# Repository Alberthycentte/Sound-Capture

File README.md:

# Sound Capture Device - User Manual By Albert Hycentte

## 📖 Table of Contents
1. [Introduction](#introduction)
2. [Hardware Overview](#hardware-overview)
3. [Getting Started](#getting-started)
4. [Operating Instructions](#operating-instructions)
5. [LED Status Indicators](#led-status-indicators)
6. [Technical Specifications](#technical-specifications)
7. [Firmware Upload Guide](#firmware-upload-guide)
8. [Troubleshooting](#troubleshooting)
9. [File Management](#file-management)
10. [Maintenance & Care](#maintenance--care)
11. [Advanced Configuration](#advanced-configuration)
12. [Safety Information](#safety-information)

---

## 🎤 Introduction

Welcome to the **Sound Capture Device**! This portable audio recorder allows you to:
- Record high-quality audio with a professional MEMS microphone
- Store recordings as standard WAV files on an SD card
- Play back recordings through a built-in amplifier and speaker
- Operate on battery power or USB for extended recording sessions

This device is perfect for voice memos, field recordings, interviews, lectures, music practice, or any situation where you need reliable audio capture.

---

## 🔧 Hardware Overview

### Main Components

| Component | Description | Location |
|-----------|-------------|----------|
| **ESP32-S3** | Main processor | Center of PCB |
| **INMP441** | MEMS microphone | Bottom right of board |
| **MAX98357A** | Class D audio amplifier | Near speaker connector |
| **SD Card Slot** | Storage for recordings | Bottom left edge |
| **USB-C Port** | Power & programming | Top-left corner |
| **Battery Connector** | LiPo battery input | Left side |
| **Speaker Connector** | 4-8Ω speaker output | Left side |

### User Interface

#### Buttons (Bottom Edge)
```
[START]  [STOP]  [PLAY]  [BOOT]  [EN]
   │       │       │       │      │
   │       │       │       │      └─── Reset button
   │       │       │       └────────── Programming mode
   │       │       └────────────────── Play last recording
   │       └────────────────────────── Stop recording/playback
   └────────────────────────────────── Start recording
```

#### Status LED
- Located near buttons
- Provides visual feedback for all operations
- See [LED Status Indicators](#led-status-indicators) for details

---

## 🚀 Getting Started

### What You Need

**Essential:**
- ✅ Sound Capture Device
- ✅ MicroSD card (4GB - 32GB, FAT32 formatted)
- ✅ USB-C cable (for charging/programming)
- ✅ 4Ω or 8Ω speaker (2-3W rating)

**Optional:**
- 🔋 3.7V LiPo battery (1000-2000mAh recommended)
- 💻 Computer (for firmware updates)

### Initial Setup

#### Step 1: Insert SD Card
1. Power off the device
2. Insert microSD card into slot (gold contacts facing down)
3. Push until it clicks into place
4. **Important:** Card must be formatted as FAT32

#### Step 2: Connect Speaker
1. Locate the 2-pin speaker connector (SPK)
2. Connect speaker wires 
3. Use 4Ω or 8Ω speaker rated for 2-3W

#### Step 3: Power Connection

**Option A: USB Power**
- Connect USB-C cable to device
- Connect other end to USB power adapter or computer
- LED should blink twice on startup

**Option B: Battery Power**
- Connect 3.7V LiPo battery to J2 connector
- Observe polarity: RED (+), BLACK (-)
- Battery charges automatically when USB connected

#### Step 4: First Power-On
1. Connect power source
2. Wait for LED indicators:
   - 2 blinks = System starting
   - 3 blinks = Ready to use
3. Device is now ready for recording!

---

## 🎵 Operating Instructions

### Recording Audio

**Basic Recording:**
1. **Press START button** once
   - LED turns ON (solid)
   - Recording begins immediately
2. Speak or capture audio (max 60 seconds)
3. **Press STOP button** to finish
   - LED blinks 2 times
   - File saved to SD card

**Recording Tips:**
- Speak clearly at normal volume
- Avoid covering microphone hole
- Recording stops automatically after 60 seconds
- Each recording creates a new numbered file (`rec_1.wav`, `rec_2.wav`, etc.)

### Playing Back Audio

**Playing Last Recording:**
1. **Press PLAY button** once
   - LED blinks slowly (500ms intervals)
   - Last recorded file plays automatically
2. Audio plays through connected speaker
3. Playback stops automatically at end
   - Or press STOP button to interrupt

**Volume:**
- Volume is set by hardware (12dB gain)
- To adjust, modify GAIN_SLOT resistor (see Advanced Configuration)

### Stopping Operations

**Stop Recording or Playback:**
- **Press STOP button** at any time
- Current operation terminates immediately
- LED blinks to confirm stop
- File is saved (if recording) before stopping

---

## 💡 LED Status Indicators

Understanding the status LED helps you know what the device is doing:

| LED Pattern | Meaning | Action |
|-------------|---------|--------|
| **2 blinks on power-up** | System initializing | Wait 2-3 seconds |
| **3 quick blinks** | System ready | Device ready to use |
| **Solid ON** | Recording in progress | Recording audio |
| **Slow blink (500ms)** | Playing audio | Playback in progress |
| **2 blinks after stop** | File saved successfully | Recording complete |
| **3 blinks (play press)** | No recordings found | Record something first |
| **5 rapid blinks** | Error detected | Check SD card or connections |
| **Continuous rapid blinks** | Critical error | Check troubleshooting section |

---

## 📊 Technical Specifications

### Audio Performance
| Parameter | Specification |
|-----------|---------------|
| **Sample Rate** | 16 kHz (voice optimized) |
| **Bit Depth** | 16-bit |
| **Channels** | Mono |
| **Format** | WAV (PCM uncompressed) |
| **Frequency Response** | 50 Hz - 8 kHz |
| **Microphone SNR** | 61 dB |
| **Amplifier Output** | 3.2W @ 4Ω, 1.4W @ 8Ω |
| **THD+N** | < 1% @ 1kHz |

### Recording Capacity
| SD Card Size | Recording Time @ 16kHz |
|--------------|------------------------|
| 4 GB | ~74 hours |
| 8 GB | ~148 hours |
| 16 GB | ~296 hours |
| 32 GB | ~592 hours |

**File Size:** Approximately 1.8 MB per minute of recording

### Power Specifications
| Mode | Current Draw | Battery Life (1000mAh) |
|------|--------------|------------------------|
| **Idle** | 50 mA | ~20 hours |
| **Recording** | 150 mA | ~6.5 hours |
| **Playback (medium volume)** | 250 mA | ~4 hours |
| **Charging** | Up to 1000 mA | ~1.5 hours |

### Physical Specifications
- **Supply Voltage:** 5V USB or 3.7V LiPo battery
- **Operating Temperature:** 0°C to 50°C
- **Storage Temperature:** -20°C to 60°C
- **Humidity:** 10% to 85% non-condensing

---

## 💻 Firmware Upload Guide

### Prerequisites

**Software Requirements:**
- Visual Studio Code (recommended) or Arduino IDE
- PlatformIO extension (for VS Code)
- USB-C cable
- Computer (Windows/Mac/Linux)

### Installation Steps

#### 1. Install PlatformIO
```bash
# For VS Code users:
1. Open VS Code
2. Go to Extensions (Ctrl+Shift+X)
3. Search "PlatformIO IDE"
4. Click Install

# For command line:
pip install platformio
```

#### 2. Prepare Project
```
Create folder structure:
sound_capture/
├── platformio.ini
├── src/
│   └── main.cpp
└── include/
```

#### 3. Configure platformio.ini
```ini
[env:esp32-s3-devkitc-1]
platform = espressif32
board = esp32-s3-devkitc-1
framework = arduino
upload_speed = 921600
monitor_speed = 115200
```

#### 4. Upload Firmware

**Method A: Using VS Code**
1. Connect USB-C cable to device
2. Hold **BOOT button** (GPIO0)
3. Press and release **EN button**
4. Release **BOOT button**
5. Click "Upload" in PlatformIO toolbar
6. Wait for "SUCCESS" message

**Method B: Command Line**
```bash
cd sound_capture
pio run --target upload
```

#### 5. Verify Upload
```bash
# Open serial monitor
pio device monitor

# You should see:
=== Sound Capture Device ===
Initializing...
System ready!
```

### Firmware Updates
To update firmware in the future:
1. Download new firmware release
2. Follow upload steps above
3. Your recordings on SD card are preserved
4. Settings may need reconfiguration

---

## 🔧 Troubleshooting

### SD Card Issues

**Problem: "SD card mount failed"**
- ✅ Check card is fully inserted
- ✅ Format card as FAT32 (not exFAT or NTFS)
- ✅ Try a different SD card
- ✅ Clean SD card contacts
- ✅ Use card 32GB or smaller

**Problem: "Failed to create file"**
- ✅ Check SD card is not write-protected
- ✅ Ensure card has free space
- ✅ Verify card is formatted correctly
- ✅ Try creating `/recordings` folder manually

### Audio Issues

**Problem: No sound when recording**
- ✅ Check microphone is not blocked
- ✅ Speak louder or move closer (6-12 inches)
- ✅ Verify INMP441 power (3.3V)
- ✅ Check GPIO36, 37, 38 connections
- ✅ Test with different recording

**Problem: No sound during playback**
- ✅ Verify speaker is connected
- ✅ Check speaker impedance (4-8Ω)
- ✅ Ensure volume is adequate (hardware gain)
- ✅ Test speaker with another device
- ✅ Check GPIO3 is enabling amplifier

**Problem: Distorted or garbled audio**
- ✅ Reduce volume (change GAIN_SLOT)
- ✅ Don't speak too close to microphone
- ✅ Check for loose connections
- ✅ Verify sample rate (16kHz default)
- ✅ Try re-recording

### Power Issues

**Problem: Device won't turn on**
- ✅ Check USB cable is connected
- ✅ Verify battery is charged
- ✅ Try different USB power source
- ✅ Check battery polarity
- ✅ Press EN button to reset

**Problem: Battery not charging**
- ✅ Ensure USB is connected
- ✅ Check charge LED (D5) is ON
- ✅ Verify battery polarity
- ✅ Battery may be fully charged
- ✅ Wait 1-2 hours for full charge

### Button Issues

**Problem: Buttons not responding**
- ✅ Press firmly and release
- ✅ Wait 200ms between presses (debounce)
- ✅ Check device is in IDLE state
- ✅ Reset device (EN button)
- ✅ Verify GPIO connections

### Error LED Patterns

**5 rapid blinks:**
1. Check SD card is inserted
2. Verify card is formatted FAT32
3. Check all connections
4. Re-upload firmware
5. Check serial monitor for details

---

## 📁 File Management

### File Structure
```
SD Card Root/
└── recordings/
    ├── rec_1.wav
    ├── rec_2.wav
    ├── rec_3.wav
    └── ...
```

### Accessing Recordings

**On Computer:**
1. Remove SD card from device
2. Insert into computer SD card reader
3. Navigate to `recordings` folder
4. Copy WAV files to computer
5. Files can be played with any media player

**Supported Players:**
- Windows Media Player
- VLC Media Player
- QuickTime (Mac)
- Any WAV-compatible software

### File Naming
- Files automatically numbered: `rec_1.wav`, `rec_2.wav`, etc.
- Device remembers last number used
- Deleting files resets numbering to highest existing number + 1

### Storage Management

**Checking Free Space:**
- Serial monitor shows card size on startup
- Monitor: "SD Card Size: XXXXMB"

**Deleting Old Recordings:**
1. Remove SD card
2. Connect to computer
3. Delete unwanted files from `/recordings/` folder
4. Re-insert card into device
5. Next recording continues numbering

**Backup Recommendations:**
- Copy recordings to computer regularly
- Keep SD card backups
- Card can be reformatted if needed (loses all data)

---

## 🛠️ Maintenance & Care

### Daily Use
- Keep device clean and dry
- Avoid extreme temperatures
- Don't cover microphone hole
- Store in protective case when not in use

### SD Card Care
- Don't remove card while recording
- Keep contacts clean
- Avoid static discharge
- Replace every 2-3 years for reliability

### Battery Maintenance
- Charge fully before first use
- Don't fully discharge (keep above 20%)
- Charge at room temperature
- Replace if runtime significantly decreases
- Store at 40-60% charge if unused for months

### Speaker Care
- Don't exceed 3W rating
- Avoid water exposure
- Check connections periodically
- Replace if sound becomes distorted

### Cleaning
- Use dry, soft cloth for exterior
- Don't use liquids near electronics
- Compressed air can clean microphone hole
- Clean SD card slot with dry brush

### Firmware Updates
- Check for updates periodically
- Updates may add features or fix bugs
- Follow upload guide for updates
- Backup recordings before updating

---

## ⚙️ Advanced Configuration

### Changing Audio Quality

**Location:** Line 51-54 in `main.cpp`

```cpp
// Voice recording (default)
#define SAMPLE_RATE    16000
#define SAMPLE_BITS    16
#define I2S_CHANNELS   1

// Music quality
#define SAMPLE_RATE    44100  // CD quality
#define SAMPLE_BITS    16
#define I2S_CHANNELS   1      // or 2 for stereo

// Phone quality (smaller files)
#define SAMPLE_RATE    8000
```

**Effect on file size:**
- 8 kHz: ~0.9 MB/min
- 16 kHz: ~1.8 MB/min
- 44.1 kHz: ~5 MB/min

### Adjusting Recording Time

**Location:** Line 54 in `main.cpp`

```cpp
#define RECORD_TIME_MS  60000  // 60 seconds

// Change to:
#define RECORD_TIME_MS  120000  // 2 minutes
#define RECORD_TIME_MS  300000  // 5 minutes
```

### Volume Adjustment (Hardware)

**Current Configuration:**
- GAIN_SLOT connected to VSYST (5V) via 0Ω resistor (R23)
- This provides 12dB gain

**To Change Volume:**

| R23 Connection | Gain | Volume |
|----------------|------|--------|
| GND | 9dB | Quieter |
| +3.3V | 12dB | Normal (current) |
| 100K to GND | 15dB | Louder |
| Open (DNP) | 18dB | Maximum |

**To modify:** Remove R23 and connect to desired voltage

### Custom File Naming

**Location:** Line 382 in `main.cpp`

```cpp
// Default naming
currentFileName = "/recordings/rec_" + String(recordingNumber) + ".wav";

// Custom naming examples:
currentFileName = "/recordings/audio_" + String(recordingNumber) + ".wav";
currentFileName = "/recordings/memo_" + String(millis()) + ".wav";
```

### Buffer Size Optimization

**Location:** Line 57 in `main.cpp`

```cpp
#define DMA_BUF_LEN    512  // Default

// For better quality, increase:
#define DMA_BUF_LEN    1024

// For lower latency, decrease:
#define DMA_BUF_LEN    256
```

**Note:** Larger buffers = smoother recording but more memory usage

---

## ⚠️ Safety Information

### Electrical Safety
- ⚡ Use only 5V USB power supply
- ⚡ Battery: 3.7V LiPo only (1000-2000mAh)
- ⚡ Observe battery polarity
- ⚡ Don't short-circuit battery terminals
- ⚡ Disconnect power during repairs

### Battery Safety
- 🔋 Use quality LiPo batteries with protection circuit
- 🔋 Don't puncture, crush, or disassemble battery
- 🔋 Keep away from heat/fire
- 🔋 Don't charge unattended
- 🔋 Dispose properly at recycling center

### Operating Precautions
- 💧 Not waterproof - avoid moisture
- 🌡️ Don't use in extreme temperatures
- 👂 Avoid excessive speaker volume near ears
- 🎤 Microphone not for medical/safety-critical use
- 📱 May interfere with sensitive equipment

### Environmental
- ♻️ Dispose of electronics responsibly
- ♻️ Recycle batteries at designated facilities
- ♻️ Keep away from children and pets
- ♻️ Follow local e-waste regulations

---

## 📞 Support & Resources

### Getting Help
1. Check this manual first
2. Review troubleshooting section
3. Check serial monitor for error messages
4. Verify all connections
5. Try known-good components (SD card, battery, etc.)

### Technical Support
- **Serial Monitor:** Connect USB and run `pio device monitor`
- **Debug Output:** Detailed startup and operation info
- **Error Messages:** Specific problem indicators

### Additional Resources
- **ESP32-S3 Datasheet:** Technical specifications
- **INMP441 Datasheet:** Microphone specifications
- **MAX98357A Datasheet:** Amplifier details
- **PlatformIO Documentation:** Development environment

---

## 📄 Specifications Summary

| Category | Details |
|----------|---------|
| **Processor** | ESP32-S3 Dual-core @ 240MHz |
| **Memory** | 512KB RAM, 16MB Flash |
| **Microphone** | INMP441 MEMS I2S |
| **Amplifier** | MAX98357A Class D, 3.2W |
| **Storage** | MicroSD up to 32GB |
| **Power** | USB-C 5V or 3.7V LiPo |
| **Battery** | 1000-2000mAh (4-6 hours) |
| **Audio Format** | 16kHz, 16-bit, Mono WAV |
| **Dimensions** | 60mm × 90mm (approximate) |
| **Weight** | ~50g (without battery) |

---

## 🎓 Quick Start Guide

**First-Time Users:**
1. ✅ Insert FAT32-formatted SD card
2. ✅ Connect 4-8Ω speaker
3. ✅ Connect USB-C power or battery
4. ✅ Wait for 3 LED blinks (ready)
5. ✅ Press START to record
6. ✅ Press STOP when done
7. ✅ Press PLAY to listen
8. ✅ Enjoy your recordings!

---

## 📜 Version History

**v1.0.0** (Current)
- Initial release
- Basic record/play/stop functionality
- WAV file format support
- Auto-numbering system
- Power management
- Status LED indicators

---

## 📝 Notes

- Device designed for voice recording applications
- Not intended for professional music production
- Recordings are mono (single channel)
- Maximum 60 seconds per recording (configurable)
- SD card required for operation
- Speaker required for playback
- Battery optional (can run from USB)

---

**Thank you for choosing the Sound Capture Device!**

For firmware updates, bug reports, or feature requests, please refer to the project repository or contact technical support.

**Happy Recording! 🎤🎵**

---

*Manual Version: 1.0.0*  
*Last Updated: 2025*  
*Compatible with Firmware: v1.0.0*

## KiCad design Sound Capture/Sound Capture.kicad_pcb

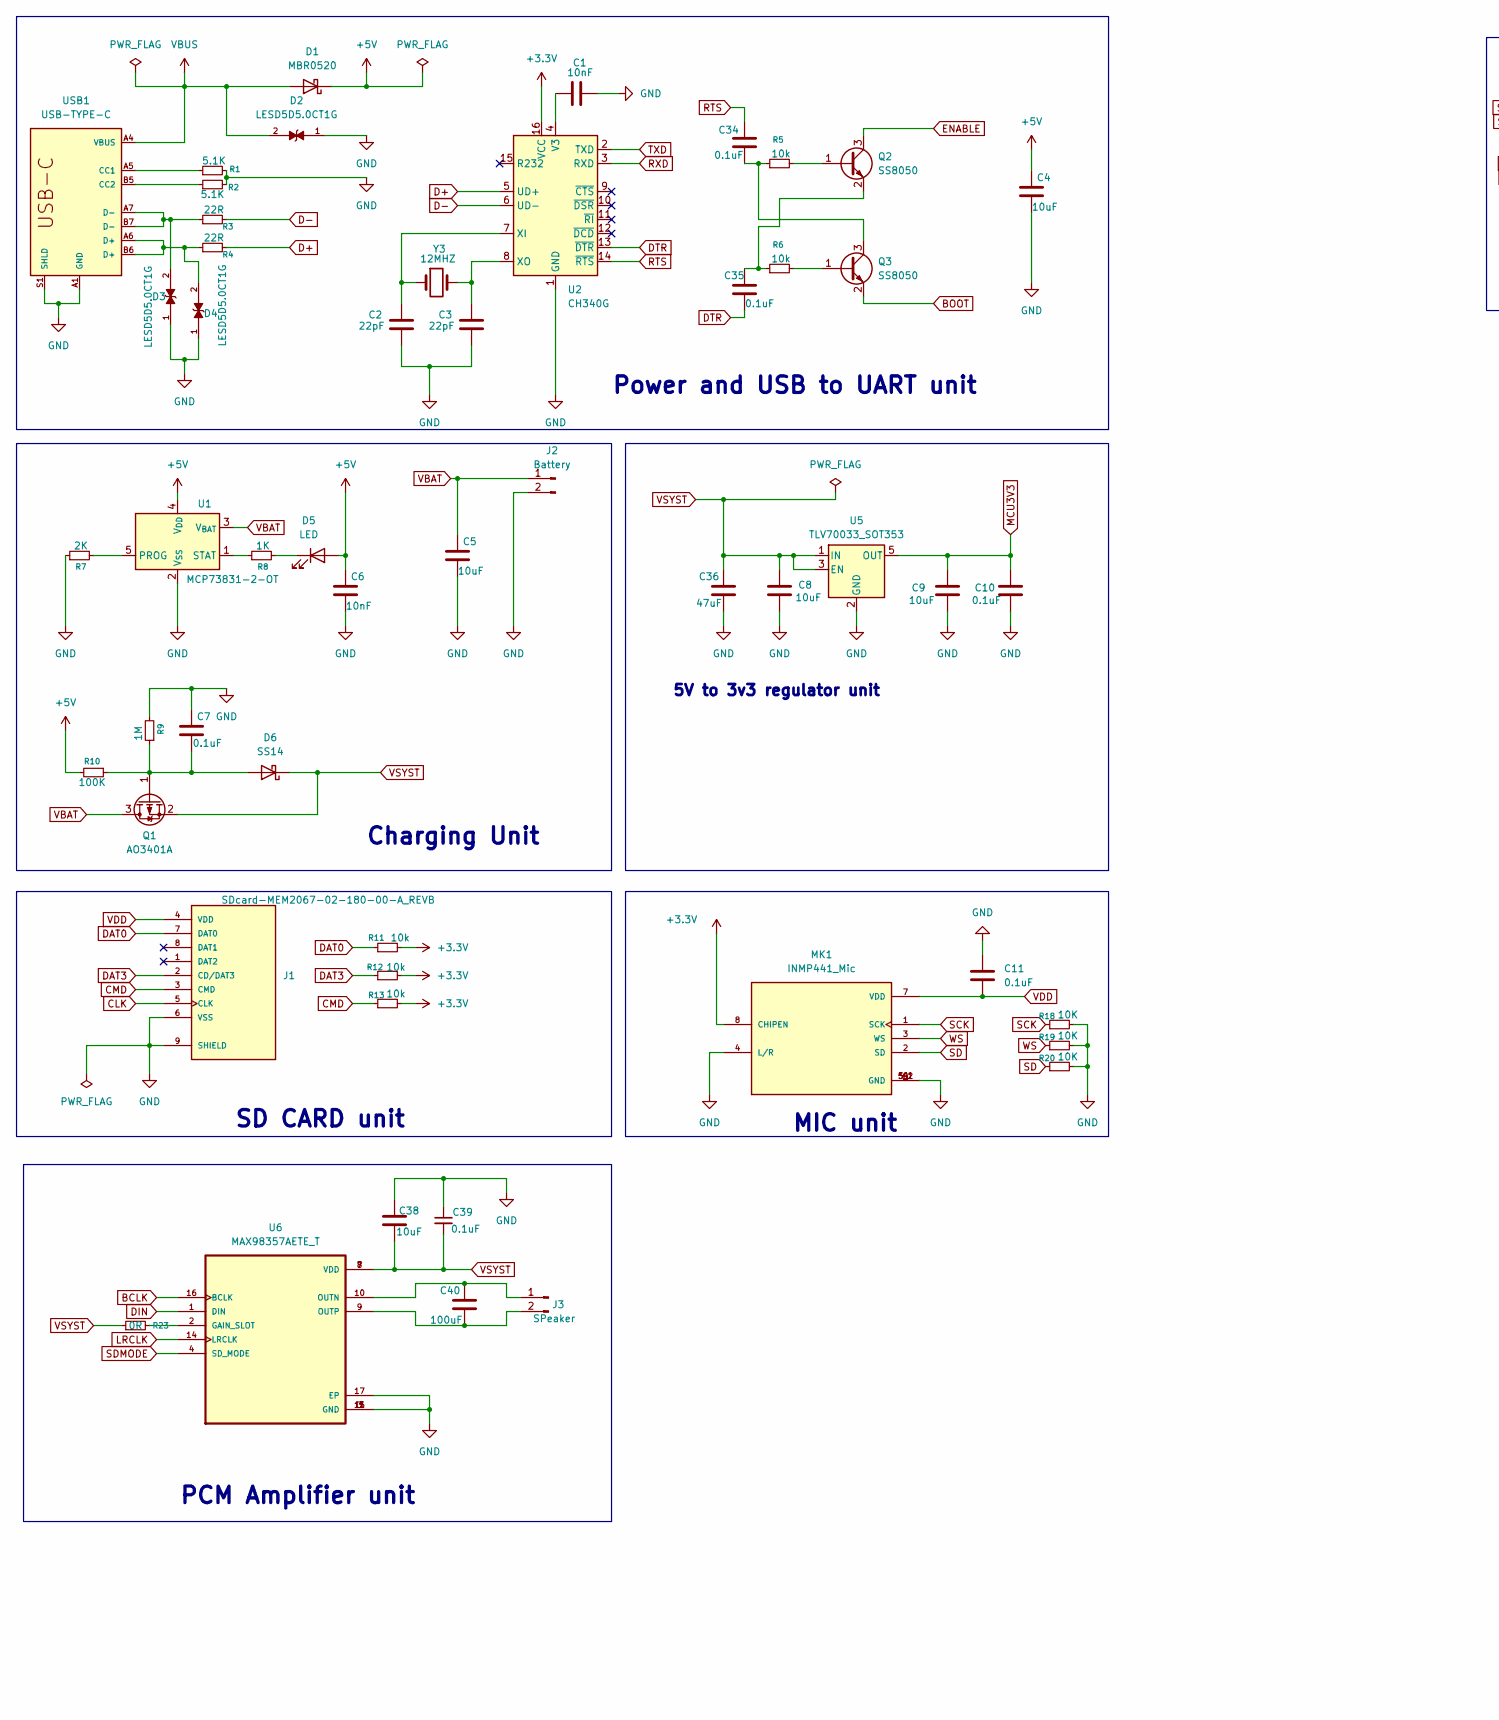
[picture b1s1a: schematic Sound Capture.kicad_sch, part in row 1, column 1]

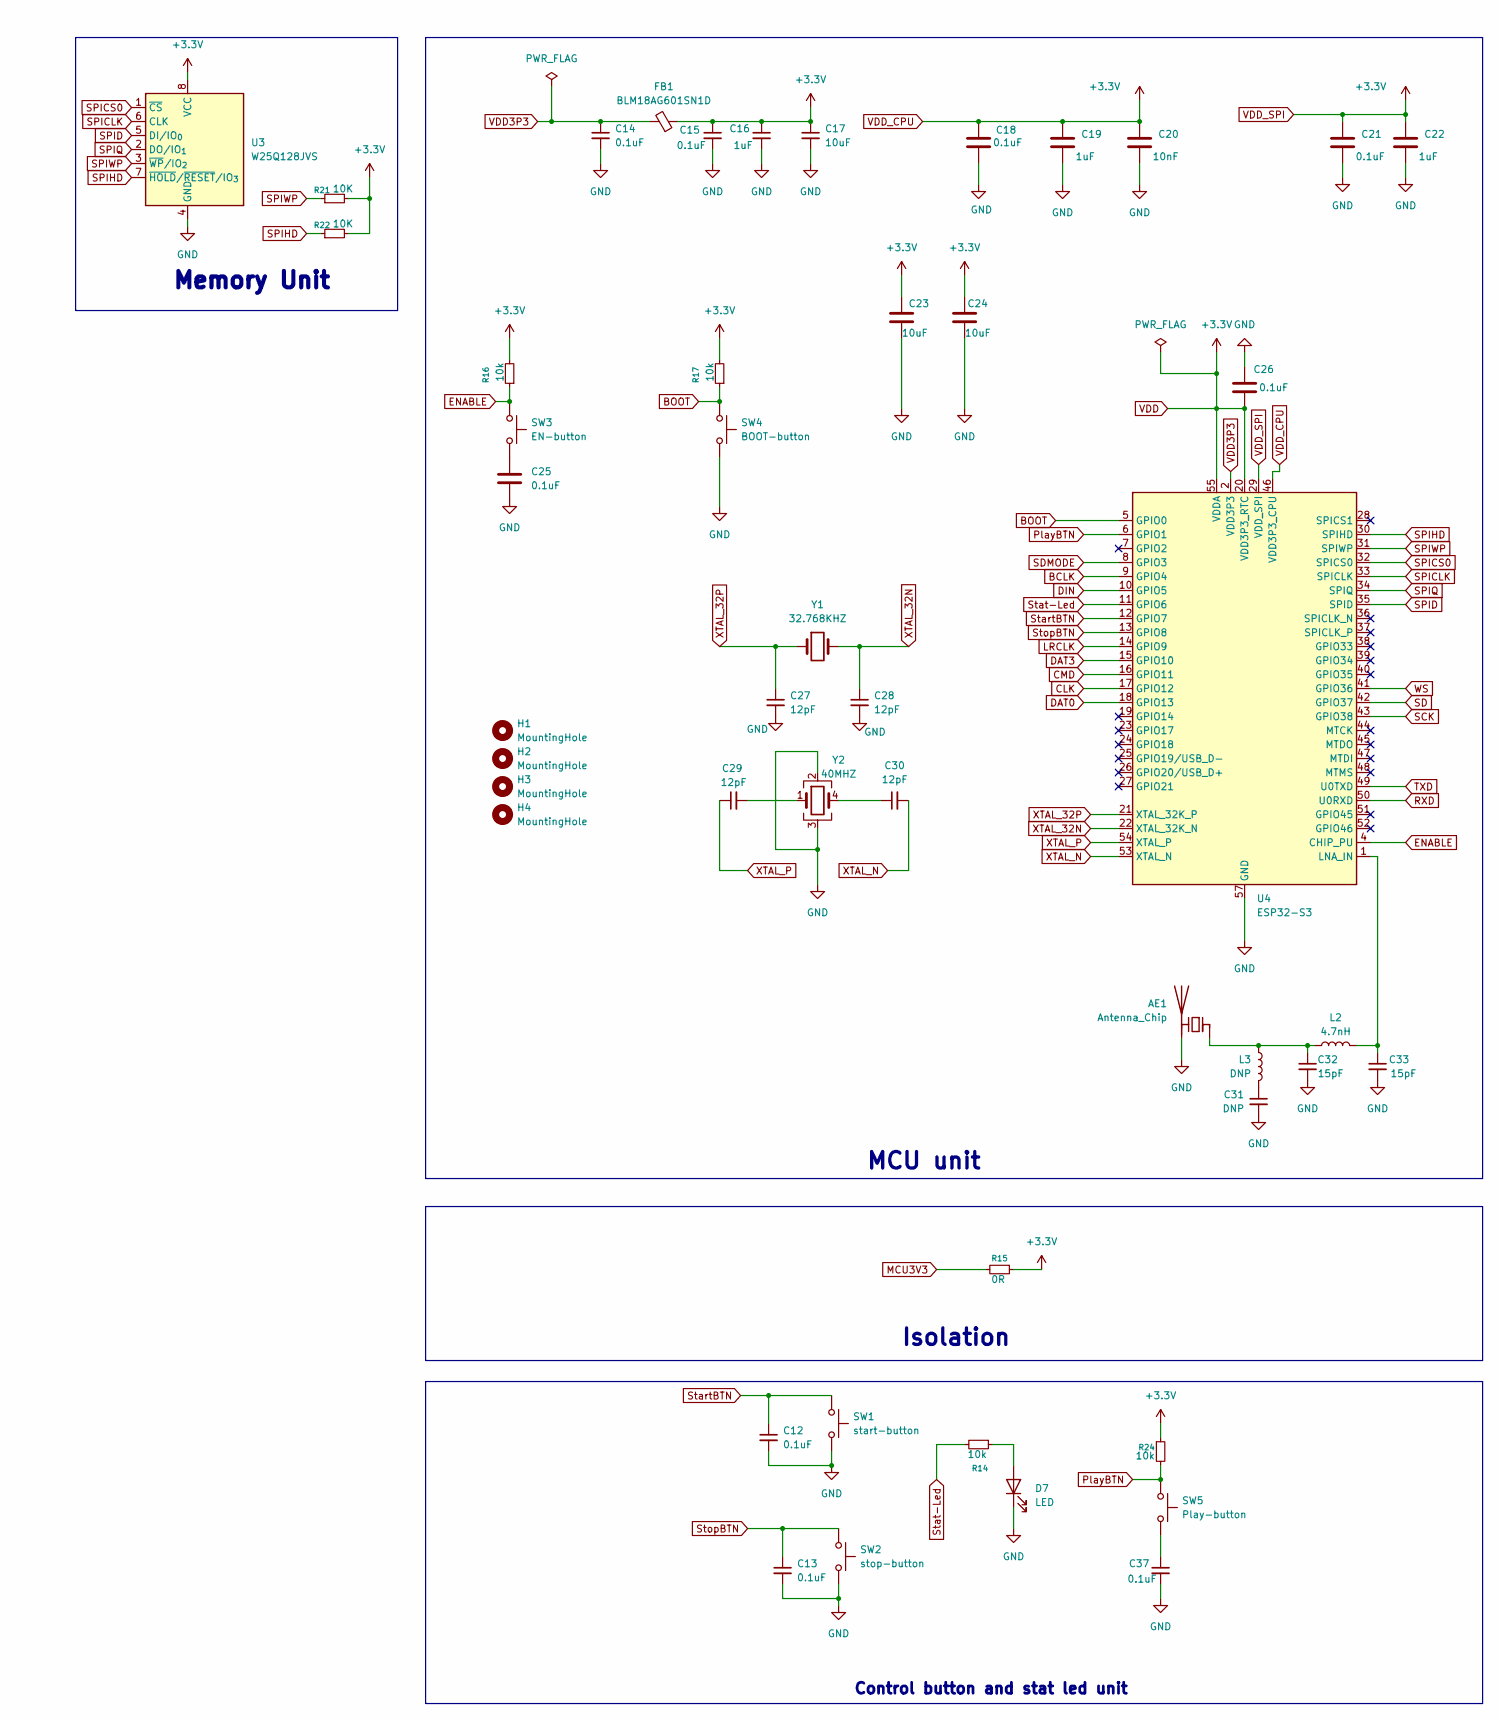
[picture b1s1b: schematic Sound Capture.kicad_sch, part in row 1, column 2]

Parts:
AE1: Antenna_Chip; Texas_SWRA117D_2.4GHz_Left
C1, C6, C20: 10nF; C_0603_1608Metric
C2, C3: 22pF; C_0603_1608Metric
C4, C5, C8, C9, C23, C24, C38: 10uF; C_1206_3216Metric
C7, C10, C11, C18, C21, C25, C26, C34, C35: 0.1uF; C_0603_1608Metric
C12, C13, C14, C15, C37, C39: 0.1uF; C_0402_1005Metric
C16: 1uF; C_0402_1005Metric
C17: 10uF; C_0402_1005Metric
C19, C22: 1uF; C_0805_2012Metric
C27, C28, C29, C30: 12pF; C_0402_1005Metric
C31: DNP; C_0402_1005Metric
C32, C33: 15pF; C_0402_1005Metric
C36: 47uF; C_1210_3225Metric
C40: 100uF; C_1210_3225Metric
D1: MBR0520; D_SOD-123
D2, D3, D4: LESD5D5.0CT1G; TVS_LESD5D5.0CT1G; PARTREV O
D5, D7: LED; LED_0805_2012Metric
D6: SS14; D_SMA
FB1: BLM18AG601SN1D; BEADC1608X95N
H1, H2, H3, H4: MountingHole; MountingHole_2.5mm_Pad
J1: SDcard-MEM2067-02-180-00-A_REVB
J2: Battery; JST_XH_B2B-XH-A_1x02_P2.50mm_Vertical
J3: SPeaker; JST_XH_B2B-XH-A_1x02_P2.50mm_Vertical
L2: 4.7nH; L_0402_1005Metric
L3: DNP; L_0402_1005Metric
MK1: INMP441_Mic; MIC_INMP441
Q1: AO3401A; SOT-23
Q2, Q3: SS8050; SOT-23
R1, R2: 5.1K; R_0805_2012Metric
R3, R4: 22R; R_0805_2012Metric
R5, R6, R11, R12, R13, R14, R16, R17, R24: 10k; R_0603_1608Metric
R7: 2K; R_0603_1608Metric
R8: 1K; R_0603_1608Metric
R9: 1M; R_0603_1608Metric
R10: 100K; R_0603_1608Metric
R15: 0R; R_0603_1608Metric
R18, R19, R20, R21, R22: 10K; R_0603_1608Metric
R23: 0R; R_0805_2012Metric
SW1: start-button; SW_PUSH_6mm
SW2: stop-button; SW_PUSH_6mm
SW3: EN-button; SW_PUSH_6mm_H5mm
SW4: BOOT-button; SW_PUSH_6mm_H5mm
SW5: Play-button; SW_PUSH_6mm
U1: MCP73831-2-OT; SOT-23-5
U2: CH340G; SOIC-16_3.9x9.9mm_P1.27mm
U3: W25Q128JVS; SOIC-8_5.3x5.3mm_P1.27mm
U4: ESP32-S3; QFN-56-1EP_7x7mm_P0.4mm_EP4x4mm
U5: TLV70033_SOT353; SOT-353_SC-70-5
U6: MAX98357AETE_T; MAX98357AETE+T -QFN50P300X300X80-17N
USB1: USB-TYPE-C; USBC.USB4110-GF-A
Y1: 32.768KHZ; Crystal_SMD_3215-2Pin_3.2x1.5mm
Y2: 40MHZ; Crystal_SMD_2520-4Pin_2.5x2.0mm
Y3: 12MHZ; XTAL_ABLS2-12.000MHZ-D4Y-T

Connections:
+5V: C4.1, C6.1, D1.1 (K), D5.2 (A), R10.2, U1.4 (V_{DD})
BCLK: U4.9 (GPIO4), U6.16 (BCLK)
BOOT: Q3.2 (E), R17.1, SW4.1, U4.5 (GPIO0)
CLK: J1.5 (CLK), U4.17 (GPIO12)
CMD: J1.3 (CMD), R13.1, U4.16 (GPIO11)
D+: R4.2, U2.5 (UD+)
D-: R3.2, U2.6 (UD-)
DAT0: J1.7 (DAT0), R11.1, U4.18 (GPIO13)
DAT3: J1.2 (CD/DAT3), R12.1, U4.15 (GPIO10)
DIN: U4.10 (GPIO5), U6.1 (DIN)
DTR: C35.1, U2.13 (~DTR)
ENABLE: Q2.3 (C), R16.1, SW3.1, U4.4 (CHIP_PU)
GND: AE1.2 (PCB_Trace), C1.2, C2.1, C3.1, C4.2, C5.2, C6.2, C7.1, C8.1, C9.1, C10.1, C11.1, C12.2, C13.2, C14.2, C15.2, C16.2, C17.2, C18.1, C19.1, C20.1, C21.1, C22.1, C23.2, C24.2, C25.2, C26.2, C27.2, C28.2, C31.2, C32.2, C33.2, C36.1, C37.2, C38.1, C39.1, D2.1, D3.1, D4.1, D7.1 (K), J1.6 (VSS), J1.9 (SHIELD), J2.2, MK1.4 (L/R), MK1.5_1 (GND), MK1.5_2 (GND), MK1.6 (GND), MK1.9 (GND), R1.2, R2.2, R7.1, R9.2, R18.2, R19.2, R20.2, SW1.2, SW2.2, SW4.2, U1.2 (V_{SS}), U2.1 (GND), U3.4 (GND), U4.57 (GND), U5.2 (GND), U6.3 (GND), U6.11 (GND), U6.15 (GND), U6.17 (EP), USB1.A1 (GND), USB1.S1 (SHLD), Y2.2, Y2.3
LRCLK: U4.14 (GPIO9), U6.14 (LRCLK)
MCU3V3: C9.2, C10.2, R15.2, U5.5 (OUT)
unnamed: AE1.1 (FEED), C32.1, L2.2, L3.2
unnamed: C25.1, SW3.2
unnamed: C29.2, Y2.1
unnamed: C30.1, Y2.4
unnamed: C31.1, L3.1
unnamed: C37.1, SW5.2
unnamed: D3.2, R3.1, USB1.A7 (D-), USB1.B7 (D-)
unnamed: D4.2, R4.1, USB1.A6 (D+), USB1.B6 (D+)
unnamed: D5.1 (K), R8.2
unnamed: C7.2, D6.2 (A), Q1.1 (G), R9.1, R10.1
unnamed: D7.2 (A), R14.1
unnamed: C40.2, J3.1, U6.10 (OUTN)
unnamed: C40.1, J3.2, U6.9 (OUTP)
unnamed: Q2.1 (B), R5.2
unnamed: C35.2, Q2.2 (E), R6.1
unnamed: Q3.1 (B), R6.2
unnamed: C34.1, Q3.3 (C), R5.1
unnamed: R7.2, U1.5 (PROG)
unnamed: R8.1, U1.1 (STAT)
unnamed: C1.1, U2.4 (V3)
unnamed: C2.2, U2.7 (XI), Y3.1
unnamed: C3.2, U2.8 (XO), Y3.2
unnamed: C33.1, L2.1, U4.1 (LNA_IN)
unnamed: R23.2, U6.2 (GAIN_SLOT)
unnamed: R1.1, USB1.A5 (CC1)
unnamed: R2.1, USB1.B5 (CC2)
PlayBTN: R24.2, SW5.1, U4.6 (GPIO1)
RTS: C34.2, U2.14 (~RTS)
RXD: U2.3 (RXD), U4.50 (U0RXD)
SCK: MK1.1 (SCK), R18.1, U4.43 (GPIO38)
SD: MK1.2 (SD), R20.1, U4.42 (GPIO37)
SDMODE: U4.8 (GPIO3), U6.4 (SD_MODE)
SPICLK: U3.6 (CLK), U4.33 (SPICLK)
SPICS0: U3.1 (~CS), U4.32 (SPICS0)
SPID: U3.5 (DI/IO_{0}), U4.35 (SPID)
SPIHD: R22.1, U3.7 (~HOLD/~RESET/IO_{3}), U4.30 (SPIHD)
SPIQ: U3.2 (DO/IO_{1}), U4.34 (SPIQ)
SPIWP: R21.1, U3.3 (~WP/IO_{2}), U4.31 (SPIWP)
StartBTN: C12.1, SW1.1, U4.12 (GPIO7)
Stat-Led: R14.2, U4.11 (GPIO6)
StopBTN: C13.1, SW2.1, U4.13 (GPIO8)
TXD: U2.2 (TXD), U4.49 (U0TXD)
VBAT: C5.1, J2.1, Q1.3 (D), U1.3 (V_{BAT})
VBUS: D1.2 (A), D2.2, USB1.A4 (VBUS)
VDD: C11.2, C15.1, C16.1, C17.1, C18.2, C19.2, C20.2, C21.2, C22.2, C23.1, C24.1, C26.1, FB1.1, J1.4 (VDD), MK1.7 (VDD), MK1.8 (CHIPEN), R11.2, R12.2, R13.2, R15.1, R16.2, R17.2, R21.2, R22.2, R24.1, U2.16 (VCC), U3.8 (VCC), U4.20 (VDD3P3_RTC), U4.29 (VDD_SPI), U4.46 (VDD3P3_CPU), U4.55 (VDDA), U4.56 (VDDA)
VDD3P3: C14.1, FB1.2, U4.2 (VDD3P3), U4.3 (VDD3P3)
VSYST: C8.2, C36.2, C38.2, C39.2, D6.1 (K), Q1.2 (S), R23.1, U5.1 (IN), U5.3 (EN), U6.7 (VDD), U6.8 (VDD)
WS: MK1.3 (WS), R19.1, U4.41 (GPIO36)
XTAL_32N: C28.1, U4.22 (XTAL_32K_N), Y1.2
XTAL_32P: C27.1, U4.21 (XTAL_32K_P), Y1.1
XTAL_N: C30.2, U4.53 (XTAL_N)
XTAL_P: C29.1, U4.54 (XTAL_P)

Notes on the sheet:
MCU unit
PCM Amplifier unit
Power and USB to UART unit
SD CARD unit
Isolation
Control button and stat led unit
MIC unit
5V to 3v3 regulator unit
Charging Unit
Memory Unit

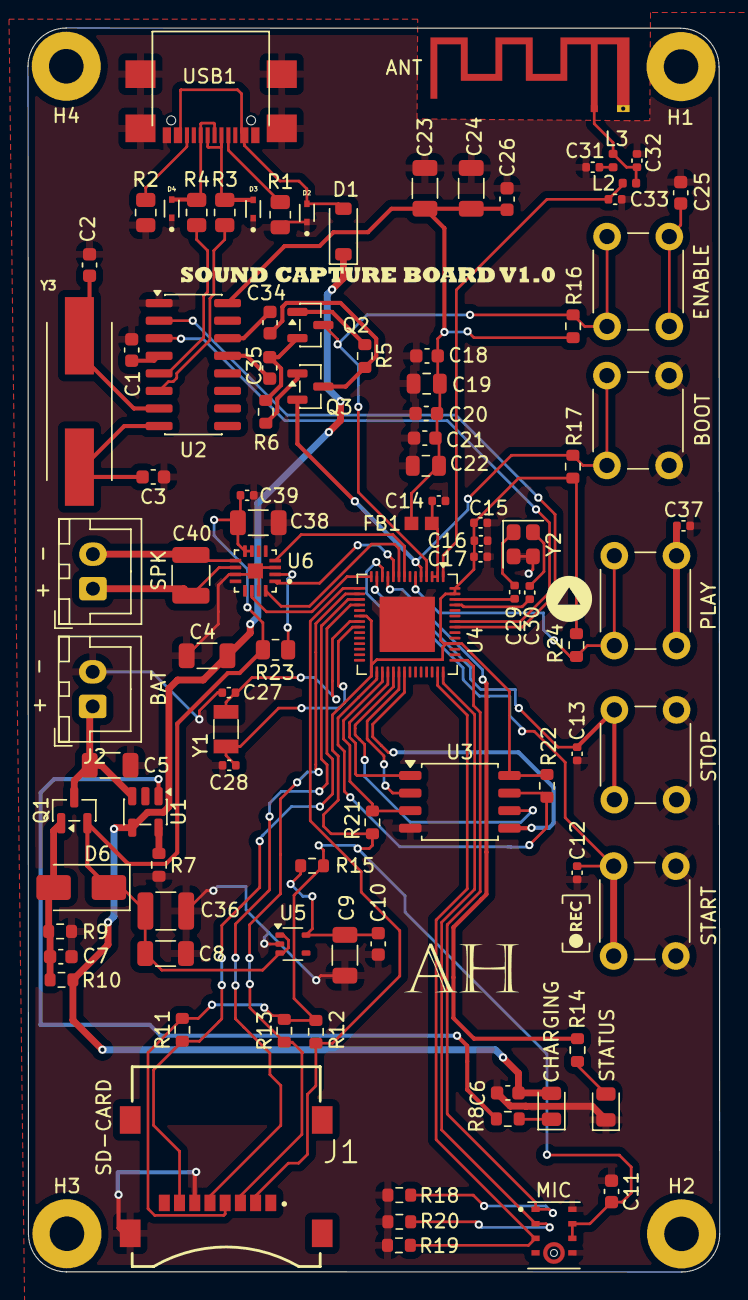
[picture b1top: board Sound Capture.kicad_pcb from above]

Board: 2 copper layers, 50.0 x 90.0 mm, 101 parts (0 on the bottom side), 67 nets.

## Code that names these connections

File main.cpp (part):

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 * Features: Record, Play, Stop with SD card storage
 * 
 * Hardware Configuration:
 * - Microphone: INMP441 (I2S Input on GPIO36, 37, 38)
 * - Amplifier: MAX98357A (I2S Output on GPIO4, 5, 9)
 * - SD Card: SPI mode (GPIO10, 11, 12, 13)
 * - Buttons: Start (GPIO7), Stop (GPIO8), Play (GPIO1)
 * - Status LED: GPIO6
 * - Amplifier Enable: GPIO3
 */

#include <Arduino.h>
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
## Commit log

2025-10-19 Revise README for Sound Capture Device user manual
    Updated README to reflect new user manual format and added detailed sections on device usage, specifications, and troubleshooting.
2025-10-19 Create Firmware
2025-10-19 Update Firmware
